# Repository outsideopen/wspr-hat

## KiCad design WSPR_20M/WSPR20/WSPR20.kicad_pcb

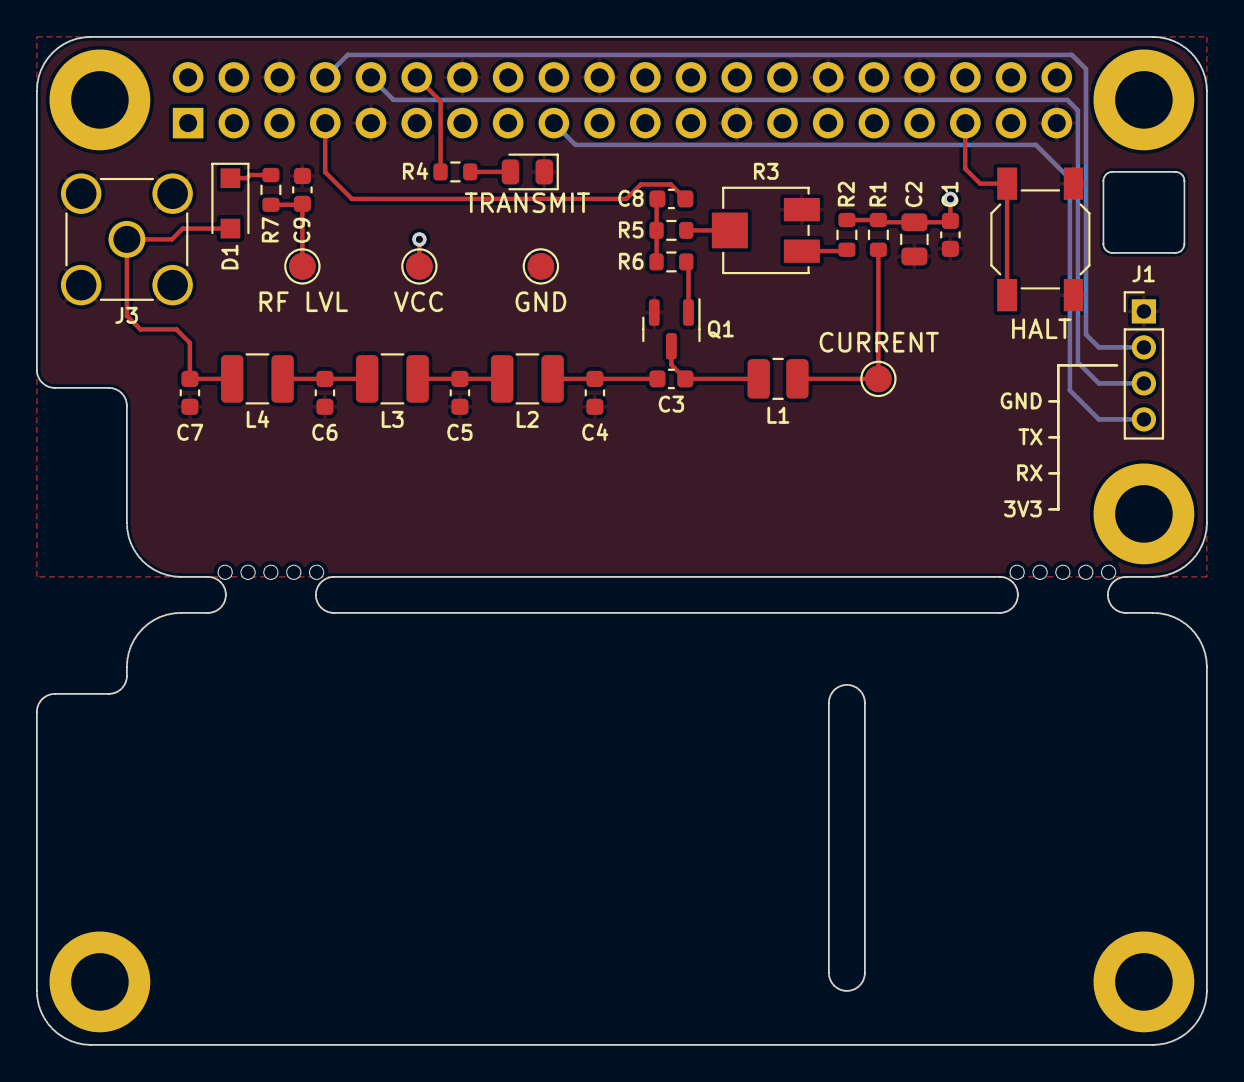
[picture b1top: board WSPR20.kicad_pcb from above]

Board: 2 copper layers, 65.0 x 56.0 mm, 38 parts (1 on the bottom side), 21 nets.

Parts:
C1, C3, C8, C9: 100nF; C_0603_1608Metric
C2: 47uF; C_0805_2012Metric
C4, C7: 470pF; C_0603_1608Metric
C5, C6: 1nF; C_0603_1608Metric
D1: 1N4148; D_SOD-123F
H1, H2, H3, H4, H5: MountingHole; MountingHole_3.2mm_M3_DIN965_Pad
H6, H7: MountingHole; mousebites
J1: SERIAL; PinHeader_1x04_P2.00mm_Vertical
J2: Conn_02x20_Odd_Even; PinSocket_2x20_P2.54mm_Vertical
J3: Conn_01x02; SMA_Amphenol_901-144_Vertical
L1: 10uH; L_1008_2520Metric
L2, L3, L4: 1.5uH; L_1210_3225Metric
LED1: LED_Small; LED_0805_2012Metric
Q1: MMBF170; SOT-23
R1: 1; R_0603_1608Metric
R2: 3.9k; R_0603_1608Metric
R3: 10k; Potentiometer_Bourns_3314J_Vertical
R4: 270; R_0603_1608Metric
R5: 10k; R_0603_1608Metric
R6: 47; R_0603_1608Metric
R7: 2K; R_0603_1608Metric
SW1: SW_SPST; SW_SPST_SKQG_WithoutStem
TP1, TP2, TP3, TP4: TestPoint; TestPoint_Pad_D1.5mm

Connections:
/3.3v: J1.4, J2.17
/RX: J1.3, J2.10
/TX: J1.2, J2.8
GND: C1.2, C2.2, C4.2, C5.2, C6.2, C7.2, C9.2, J1.1, J2.6, J2.9, J2.14, J2.20, J2.25, J2.30, J2.34, J2.39, J3.2, LED1.1 (K), Q1.2 (S), R3.3, SW1.2 (B), TP4.1
unnamed: C3.1, L1.2, Q1.3 (D)
unnamed: C3.2, C4.1, L2.1
unnamed: C5.1, L2.2, L3.1
unnamed: C6.1, L3.2, L4.1
unnamed: C8.1, J2.7
unnamed: C8.2, R5.2, R6.1
unnamed: C9.1, R7.2, TP3.1
unnamed: D1.1 (K), R7.1
unnamed: J2.12, R4.2
unnamed: J2.35, SW1.1 (A)
unnamed: C7.1, D1.2 (A), J3.1, L4.2
unnamed: L1.1, R1.2, TP2.1
unnamed: LED1.2 (A), R4.1
unnamed: Q1.1 (G), R6.2
unnamed: R2.1, R3.1
unnamed: R3.2, R5.1
VCC: C1.1, C2.1, J2.2, J2.4, R1.1, R2.2, TP1.1

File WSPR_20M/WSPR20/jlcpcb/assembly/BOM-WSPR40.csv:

Comment,Designator,Footprint,LCSC
MMBF170,Q1,SOT-23,C130879
100nF,"C1,C3,C8,C9",C_0603_1608Metric,C14663
1nF,"C5,C6",C_0603_1608Metric,C1588
470pF,"C4,C7",C_0603_1608Metric,C1620
47uF,C2,C_0805_2012Metric,C16780
1,R1,R_0603_1608Metric,C22936
270,R4,R_0603_1608Metric,C22966
2K,R7,R_0603_1608Metric,C22975
3.9k,R2,R_0603_1608Metric,C23018
47,R6,R_0603_1608Metric,C23182
10k,R5,R_0603_1608Metric,C25804
10uH,L1,L_1008_2520Metric,C295709
1.5uH,"L2,L3,L4",L_1210_3225Metric,C318053
SW_SPST,SW1,SW_SPST_SKQG_WithoutStem,C318884
10k,R3,Potentiometer_Bourns_3314J_Vertical,C36376
Conn_01x02,J3,SMA_Amphenol_901-144_Vertical,C504007
1N4148,D1,D_SOD-123F,C81598
LED_Small,LED1,LED_0805_2012Metric,C84256
MountingHole,H7,mousebites,
MountingHole,H6,mousebites,
MountingHole,H2,MountingHole_3.2mm_M3_DIN965_Pad,
MountingHole,H1,MountingHole_3.2mm_M3_DIN965_Pad,
MountingHole,H5,MountingHole_3.2mm_M3_DIN965_Pad,
MountingHole,H4,MountingHole_3.2mm_M3_DIN965_Pad,
MountingHole,H3,MountingHole_3.2mm_M3_DIN965_Pad,
Conn_02x20_Odd_Even,J2,PinSocket_2x20_P2.54mm_Vertical,
TestPoint,TP2,TestPoint_Pad_D1.5mm,
TestPoint,TP1,TestPoint_Pad_D1.5mm,
TestPoint,TP4,TestPoint_Pad_D1.5mm,
TestPoint,TP3,TestPoint_Pad_D1.5mm,
SERIAL,J1,PinHeader_1x04_P2.00mm_Vertical,

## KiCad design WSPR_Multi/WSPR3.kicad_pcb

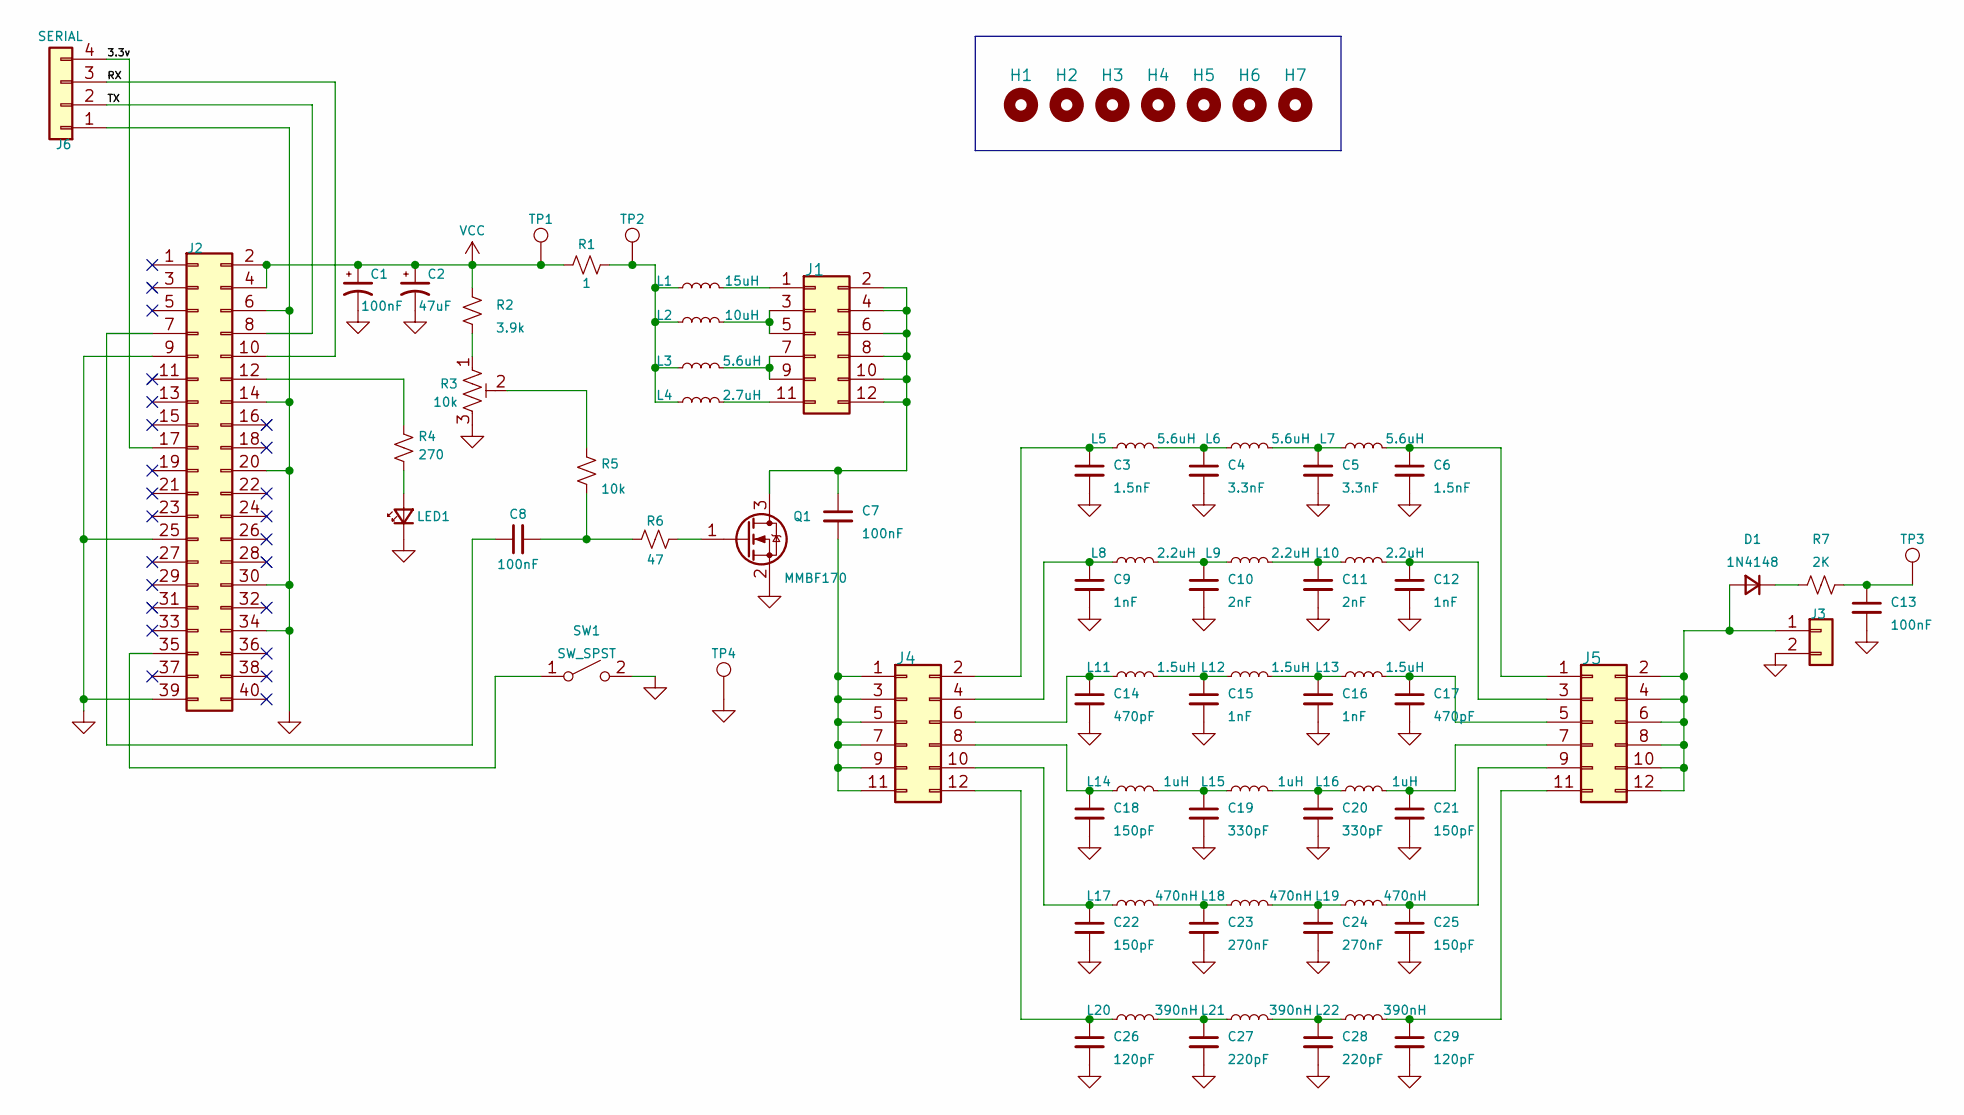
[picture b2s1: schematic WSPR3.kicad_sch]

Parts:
C1, C7, C8, C13: 100nF; C_0603_1608Metric
C2: 47uF; C_0805_2012Metric
C3, C6: 1.5nF; C_0603_1608Metric
C4, C5: 3.3nF; C_0603_1608Metric
C9, C12, C15, C16: 1nF; C_0603_1608Metric
C10, C11: 2nF; C_0603_1608Metric
C14, C17: 470pF; C_0603_1608Metric
C18, C21, C22, C25: 150pF; C_0603_1608Metric
C19, C20: 330pF; C_0603_1608Metric
C23, C24: 270nF; C_0603_1608Metric
C26, C29: 120pF; C_0603_1608Metric
C27, C28: 220pF; C_0603_1608Metric
D1: 1N4148; D_SOD-123F
H1, H2, H3, H4, H5: MountingHole; MountingHole_3.2mm_M3_DIN965_Pad
H6, H7: MountingHole; mousebites
J1, J4, J5: Conn_02x06_Odd_Even; PinHeader_2x06_P2.00mm_Vertical
J2: Conn_02x20_Odd_Even; PinSocket_2x20_P2.54mm_Vertical
J3: Conn_01x02; SMA_Amphenol_901-144_Vertical
J6: SERIAL; PinHeader_1x04_P2.00mm_Vertical
L1: 15uH; L_0805_2012Metric
L2: 10uH; L_0805_2012Metric
L3, L5, L6, L7: 5.6uH; L_0805_2012Metric
L4: 2.7uH; L_0805_2012Metric
L8, L9, L10: 2.2uH; L_0805_2012Metric
L11, L12, L13: 1.5uH; L_0805_2012Metric
L14, L15, L16: 1uH; L_0805_2012Metric
L17, L18, L19: 470nH; L_0805_2012Metric
L20, L21, L22: 390nH; L_0805_2012Metric
LED1: LED_Small; LED_0805_2012Metric
Q1: MMBF170; SOT-23
R1: 1; R_0603_1608Metric
R2: 3.9k; R_0603_1608Metric
R3: 10k; Potentiometer_Bourns_3314J_Vertical
R4: 270; R_0603_1608Metric
R5: 10k; R_0603_1608Metric
R6: 47; R_0603_1608Metric
R7: 2K; R_0603_1608Metric
SW1: SW_SPST; SW_SPST_SKQG_WithoutStem
TP1, TP2, TP3, TP4: TestPoint; TestPoint_Pad_D1.5mm

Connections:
/3.3v: J2.17, J6.4
/RX: J2.10, J6.3
/TX: J2.8, J6.2
GND: C1.2, C2.2, C3.2, C4.2, C5.2, C6.2, C9.2, C10.2, C11.2, C12.2, C13.2, C14.2, C15.2, C16.2, C17.2, C18.2, C19.2, C20.2, C21.2, C22.2, C23.2, C24.2, C25.2, C26.2, C27.2, C28.2, C29.2, J2.6, J2.9, J2.14, J2.20, J2.25, J2.30, J2.34, J2.39, J3.2, J6.1, LED1.1 (K), Q1.2 (S), R3.3, SW1.2 (B), TP4.1
unnamed: C3.1, J4.2, L5.1
unnamed: C4.1, L5.2, L6.1
unnamed: C5.1, L6.2, L7.1
unnamed: C6.1, J5.1, L7.2
unnamed: C7.1, J1.2, J1.4, J1.6, J1.8, J1.10, J1.12, Q1.3 (D)
unnamed: C7.2, J4.1, J4.3, J4.5, J4.7, J4.9, J4.11
unnamed: C8.1, J2.7
unnamed: C8.2, R5.2, R6.1
unnamed: C9.1, J4.4, L8.1
unnamed: C10.1, L8.2, L9.1
unnamed: C11.1, L9.2, L10.1
unnamed: C12.1, J5.3, L10.2
unnamed: C13.1, R7.2, TP3.1
unnamed: C14.1, J4.6, L11.1
unnamed: C15.1, L11.2, L12.1
unnamed: C16.1, L12.2, L13.1
unnamed: C17.1, J5.5, L13.2
unnamed: C18.1, J4.8, L14.1
unnamed: C19.1, L14.2, L15.1
unnamed: C20.1, L15.2, L16.1
unnamed: C21.1, J5.7, L16.2
unnamed: C22.1, J4.10, L17.1
unnamed: C23.1, L17.2, L18.1
unnamed: C24.1, L18.2, L19.1
unnamed: C25.1, J5.9, L19.2
unnamed: C26.1, J4.12, L20.1
unnamed: C27.1, L20.2, L21.1
unnamed: C28.1, L21.2, L22.1
unnamed: C29.1, J5.11, L22.2
unnamed: D1.1 (K), R7.1
unnamed: D1.2 (A), J3.1, J5.2, J5.4, J5.6, J5.8, J5.10, J5.12
unnamed: J1.1, L1.2
unnamed: J1.3, J1.5, L2.2
unnamed: J1.7, J1.9, L3.2
unnamed: J1.11, L4.2
unnamed: J2.12, R4.2
unnamed: J2.35, SW1.1 (A)
unnamed: L1.1, L2.1, L3.1, L4.1, R1.2, TP2.1
unnamed: LED1.2 (A), R4.1
unnamed: Q1.1 (G), R6.2
unnamed: R2.1, R3.1
unnamed: R3.2, R5.1
VCC: C1.1, C2.1, J2.2, J2.4, R1.1, R2.2, TP1.1

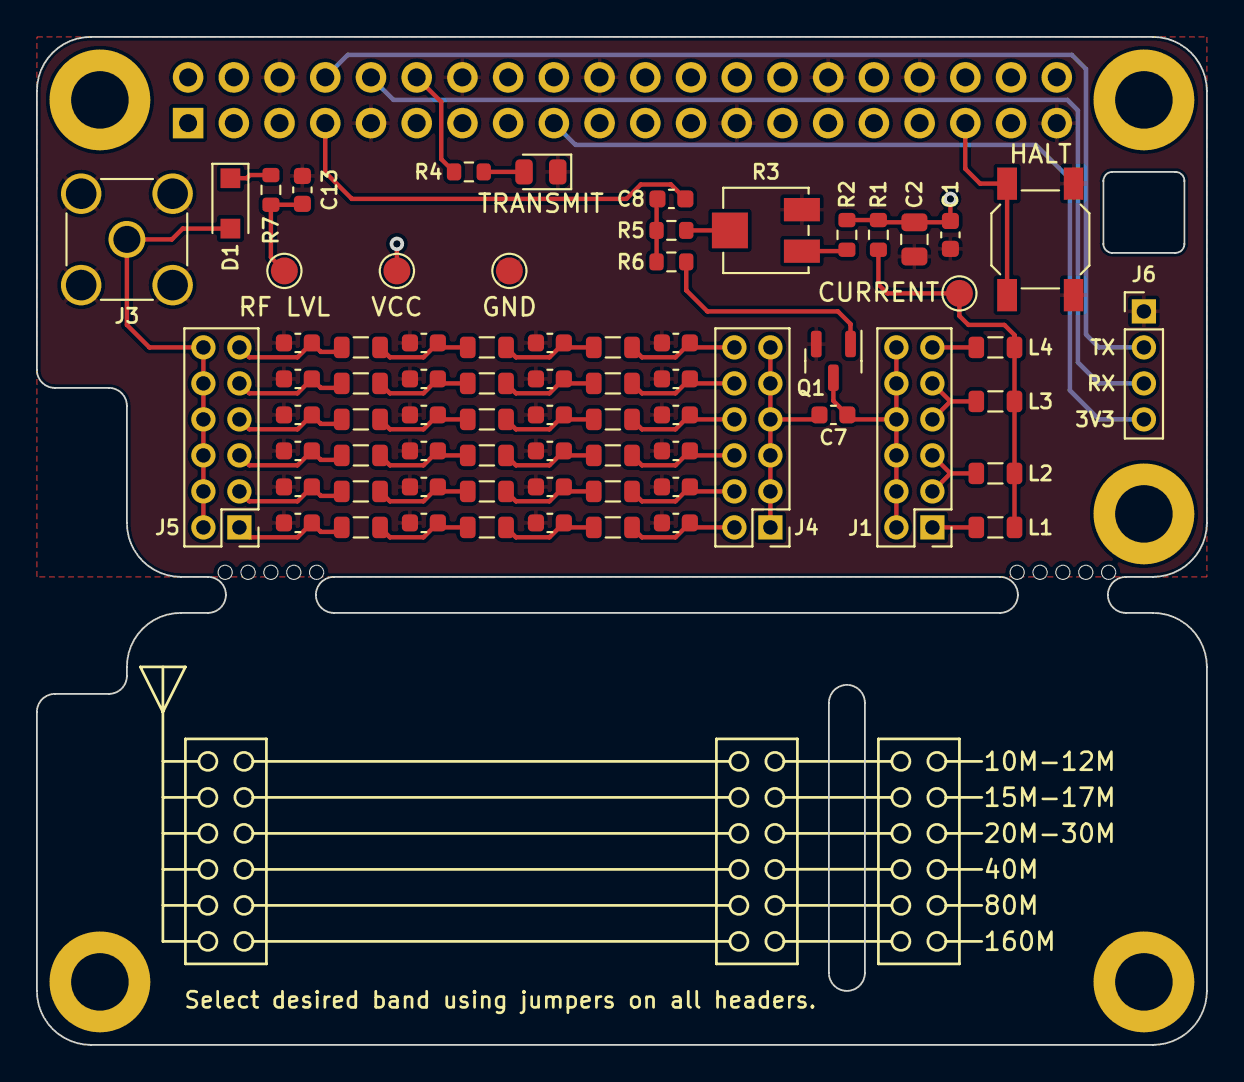
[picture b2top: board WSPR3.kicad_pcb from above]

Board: 2 copper layers, 65.0 x 56.0 mm, 79 parts (1 on the bottom side), 47 nets.

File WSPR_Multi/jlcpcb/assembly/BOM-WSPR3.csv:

Comment,Designator,Footprint,LCSC
390nH,"L20,L21,L22",L_0805_2012Metric,C108076
470nH,"L17,L18,L19",L_0805_2012Metric,C115159
MMBF170,Q1,SOT-23,C130879
100nF,"C1,C13,C7,C8",C_0603_1608Metric,C14663
1nF,"C12,C15,C16,C9",C_0603_1608Metric,C1588
150pF,"C18,C21,C22,C25",C_0603_1608Metric,C1594
1.5nF,"C3,C6",C_0603_1608Metric,C1595
2nF,"C10,C11",C_0603_1608Metric,C1601
220pF,"C27,C28",C_0603_1608Metric,C1603
3.3nF,"C4,C5",C_0603_1608Metric,C1613
470pF,"C14,C17",C_0603_1608Metric,C1620
330pF,"C19,C20",C_0603_1608Metric,C1664
47uF,C2,C_0805_2012Metric,C16780
120pF,"C26,C29",C_0603_1608Metric,C18438
1uH,"L14,L15,L16",L_0805_2012Metric,C186933
10uH,L2,L_0805_2012Metric,C186939
15uH,L1,L_0805_2012Metric,C186940
1,R1,R_0603_1608Metric,C22936
270,R4,R_0603_1608Metric,C22966
2K,R7,R_0603_1608Metric,C22975
3.9k,R2,R_0603_1608Metric,C23018
47,R6,R_0603_1608Metric,C23182
2.7uH,L4,L_0805_2012Metric,C251853
10k,R5,R_0603_1608Metric,C25804
5.6uH,"L3,L5,L6,L7",L_0805_2012Metric,C280493
SW_SPST,SW1,SW_SPST_SKQG_WithoutStem,C318884
10k,R3,Potentiometer_Bourns_3314J_Vertical,C36376
270nF,"C23,C24",C_0603_1608Metric,C376826
1.5uH,"L11,L12,L13",L_0805_2012Metric,C393989
2.2uH,"L10,L8,L9",L_0805_2012Metric,C494719
Conn_01x02,J3,SMA_Amphenol_901-144_Vertical,C504007
Conn_02x06_Odd_Even,"J1,J4,J5",PinHeader_2x06_P2.00mm_Vertical,C541867
1N4148,D1,D_SOD-123F,C81598
LED_Small,LED1,LED_0805_2012Metric,C84256
MountingHole,H7,mousebites,
MountingHole,H6,mousebites,
MountingHole,H2,MountingHole_3.2mm_M3_DIN965_Pad,
MountingHole,H1,MountingHole_3.2mm_M3_DIN965_Pad,
MountingHole,H5,MountingHole_3.2mm_M3_DIN965_Pad,
MountingHole,H4,MountingHole_3.2mm_M3_DIN965_Pad,
MountingHole,H3,MountingHole_3.2mm_M3_DIN965_Pad,
Conn_02x20_Odd_Even,J2,PinSocket_2x20_P2.54mm_Vertical,
SERIAL,J6,PinHeader_1x04_P2.00mm_Vertical,
TestPoint,TP2,TestPoint_Pad_D1.5mm,
TestPoint,TP1,TestPoint_Pad_D1.5mm,
TestPoint,TP4,TestPoint_Pad_D1.5mm,
TestPoint,TP3,TestPoint_Pad_D1.5mm,

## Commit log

2025-11-04 KiCad files
2025-11-04 Archive files added
